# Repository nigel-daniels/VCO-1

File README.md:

# VCO 1

Here is my first VCO based on the work of Moritz Klein and his great series of VCO videos found [here](https://www.youtube.com/watch?v=QBatvo8bCa4&list=PLHeL0JWdJLvTuGCyC3qvx0RM39YvopVQN). I based the schematic on his work and the Erica Synths kit schematic but I added in the sawtooth-to-triangle wave converter. 

The PCB design is my own and I designed it as a two layer pcb made of two double sided pcbs. I ended up self-etching, hence the registration pin-holes next to the drill holes for the standoffs on the pcb designs.

I hope you find this useful, and a huge thanks to Moritz Klein for getting me started down this path!

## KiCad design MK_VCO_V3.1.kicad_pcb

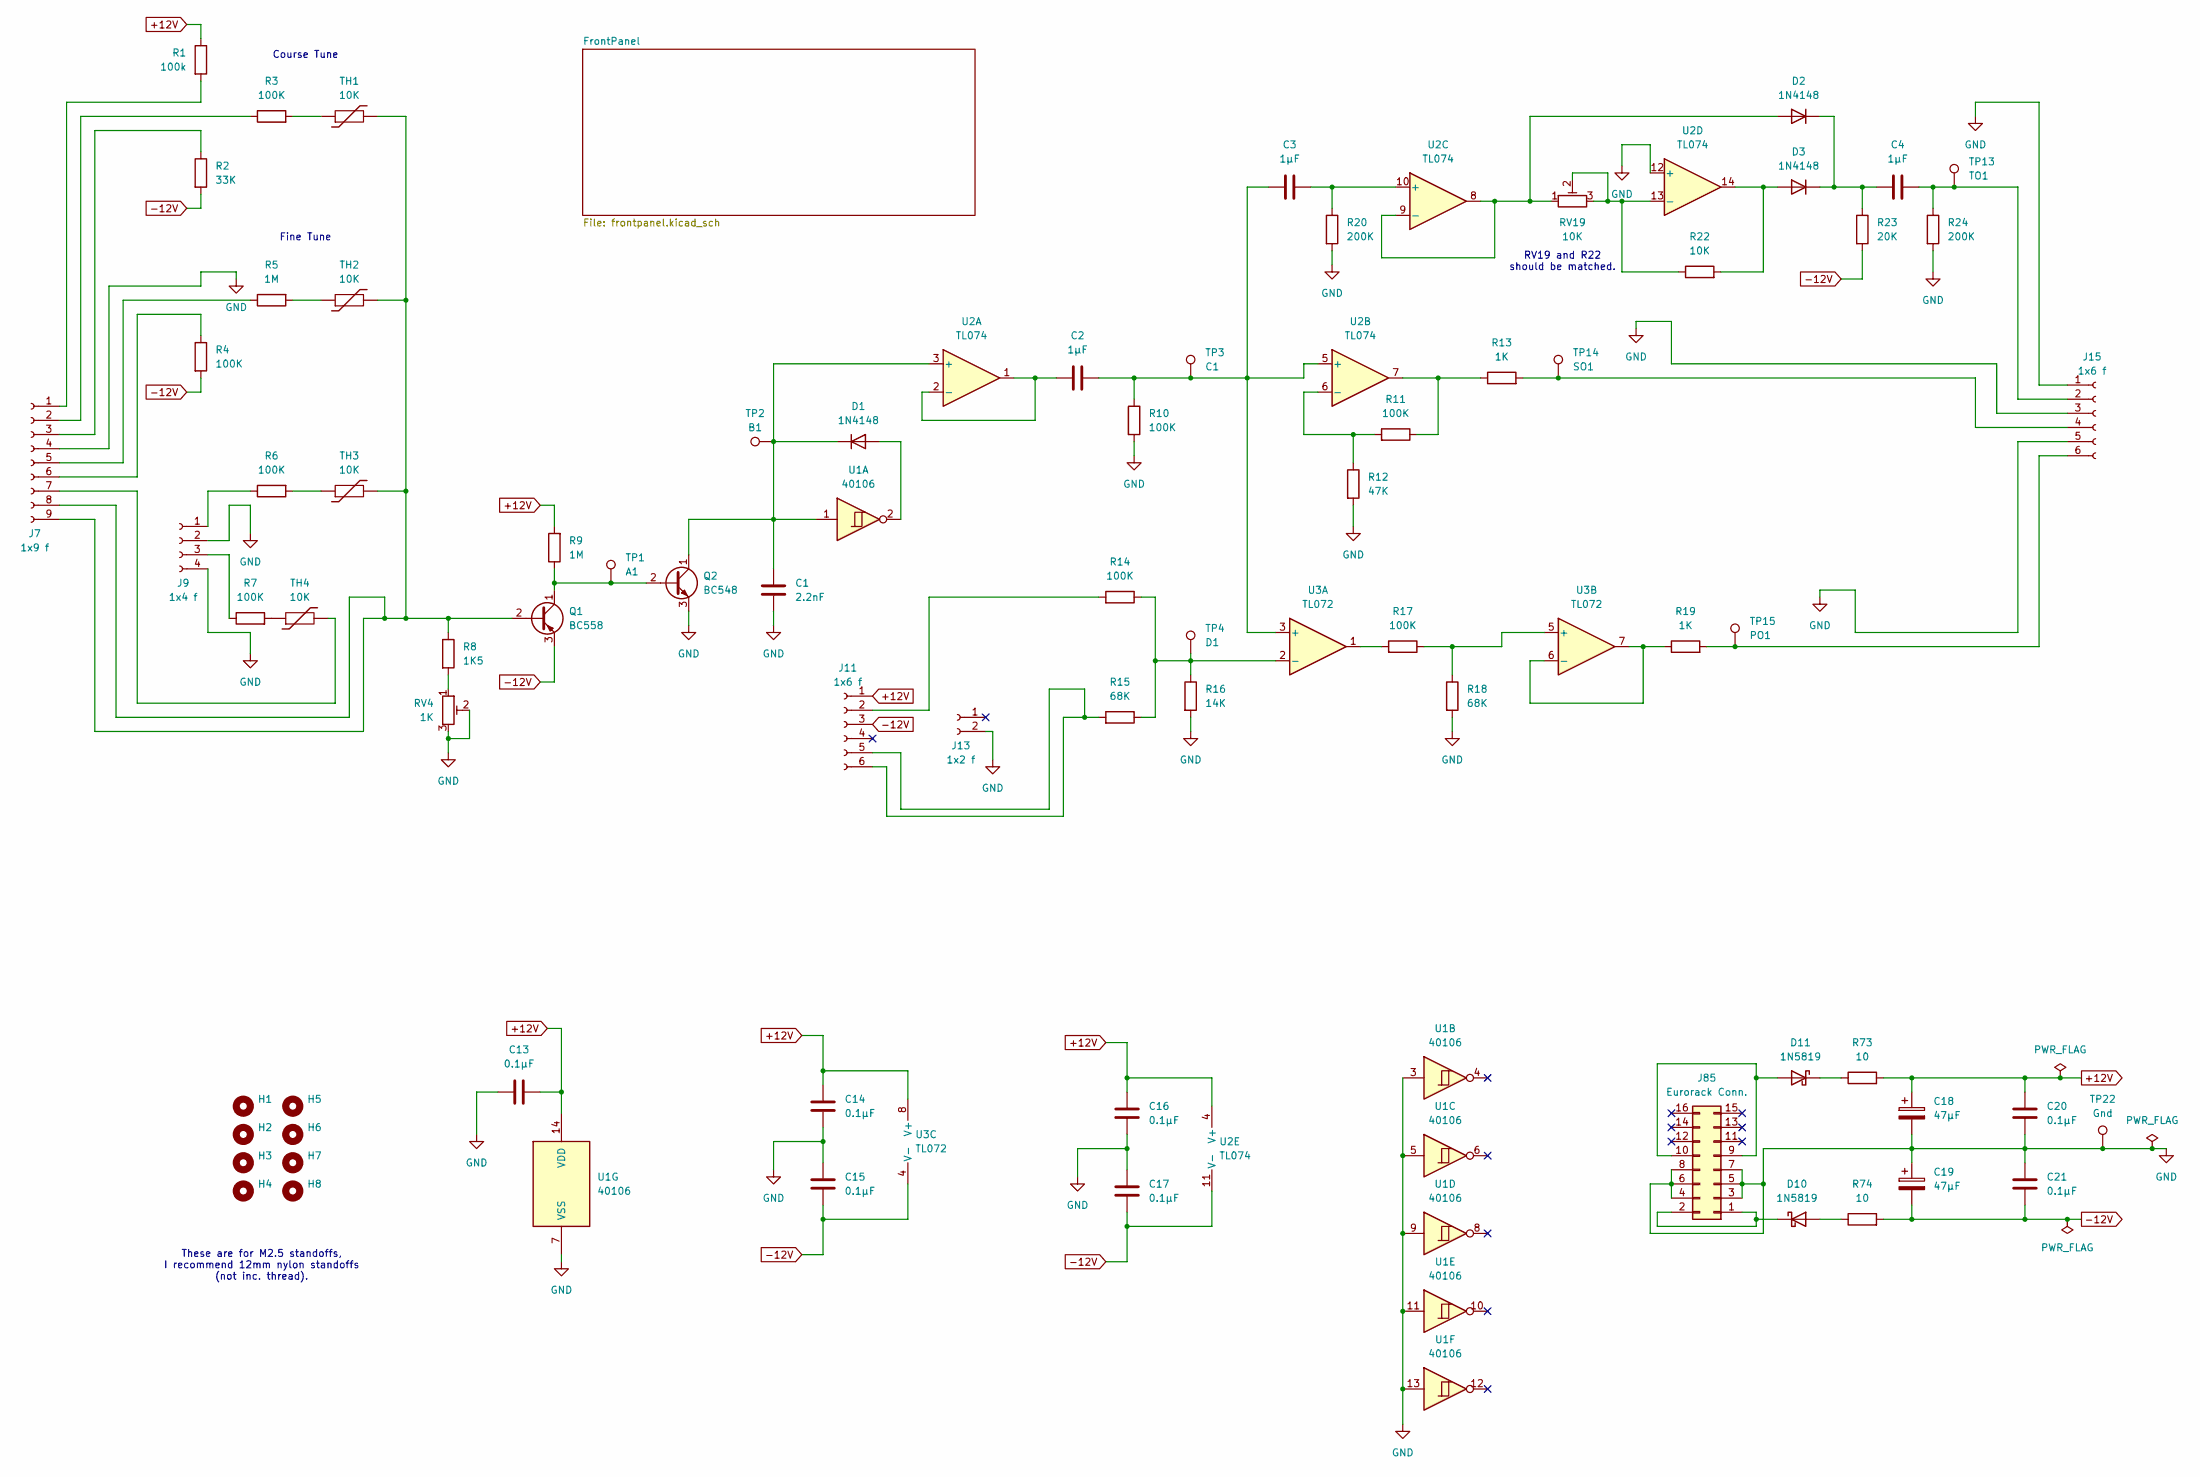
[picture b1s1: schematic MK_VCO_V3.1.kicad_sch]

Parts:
C1: 2.2nF; C_Disc_D4.7mm_W2.5mm_P5.00mm
C2, C3, C4: 1μF; C_Disc_D4.7mm_W2.5mm_P5.00mm
C13, C14, C15, C16, C17, C20, C21: 0.1μF; C_Disc_D4.7mm_W2.5mm_P5.00mm
C18, C19: 47μF; CP_Radial_D5.0mm_P2.50mm
D1: 1N4148; D_DO-35_SOD27_P2.54mm_Vertical_KathodeUp
D2, D3: 1N4148; D_DO-35_SOD27_P7.62mm_Horizontal
D10, D11: 1N5819; D_DO-41_SOD81_P10.16mm_Horizontal
H1, H2, H3, H4, H5, H6, H7, H8: MountingHole_2.7mm_M2.5
J7: 1x9 f; PinSocket_1x09_P2.54mm_Vertical
J9: 1x4 f; PinSocket_1x04_P2.54mm_Vertical
J11, J15: 1x6 f; PinSocket_1x06_P2.54mm_Vertical
J13: 1x2 f; PinSocket_1x02_P2.54mm_Vertical
J85: Eurorack Conn.; PinHeader_2x08_P2.54mm_Vertical
Q1: BC558; TO-92_Inline_Wide
Q2: BC548; TO-92_Inline_Wide
R1: 100k; R_Axial_DIN0204_L3.6mm_D1.6mm_P7.62mm_Horizontal
R2: 33K; R_Axial_DIN0204_L3.6mm_D1.6mm_P7.62mm_Horizontal
R3, R4, R6, R7, R14, R17: 100K; R_Axial_DIN0204_L3.6mm_D1.6mm_P7.62mm_Horizontal
R5, R9: 1M; R_Axial_DIN0204_L3.6mm_D1.6mm_P7.62mm_Horizontal
R8: 1K5; R_Axial_DIN0204_L3.6mm_D1.6mm_P7.62mm_Horizontal
R10, R11: 100K; R_Axial_DIN0204_L3.6mm_D1.6mm_P2.54mm_Vertical
R12: 47K; R_Axial_DIN0204_L3.6mm_D1.6mm_P2.54mm_Vertical
R13: 1K; R_Axial_DIN0204_L3.6mm_D1.6mm_P7.62mm_Horizontal
R15, R18: 68K; R_Axial_DIN0204_L3.6mm_D1.6mm_P2.54mm_Vertical
R16: 14K; R_Axial_DIN0204_L3.6mm_D1.6mm_P7.62mm_Horizontal
R19: 1K; R_Axial_DIN0204_L3.6mm_D1.6mm_P2.54mm_Vertical
R20: 200K; R_Axial_DIN0204_L3.6mm_D1.6mm_P7.62mm_Horizontal
R22: 10K; R_Axial_DIN0204_L3.6mm_D1.6mm_P2.54mm_Vertical
R23: 20K; R_Axial_DIN0204_L3.6mm_D1.6mm_P7.62mm_Horizontal
R24: 200K; R_Axial_DIN0204_L3.6mm_D1.6mm_P2.54mm_Vertical
R73, R74: 10; R_Axial_DIN0204_L3.6mm_D1.6mm_P7.62mm_Horizontal
RV4: 1K; Potentiometer_Bourns_3296W_Vertical
RV19: 10K; Potentiometer_Bourns_3296W_Vertical
TH1, TH2, TH3, TH4: 10K; R_Axial_DIN0204_L3.6mm_D1.6mm_P5.08mm_Horizontal
TP1: A1; TestPoint_Loop_D2.50mm_Drill1.0mm
TP2: B1; TestPoint_Loop_D2.50mm_Drill1.0mm
TP3: C1; TestPoint_Loop_D2.50mm_Drill1.0mm
TP4: D1; TestPoint_Loop_D2.50mm_Drill1.0mm
TP13: TO1; TestPoint_Loop_D2.50mm_Drill1.0mm
TP14: SO1; TestPoint_Loop_D2.50mm_Drill1.0mm
TP15: PO1; TestPoint_Loop_D2.50mm_Drill1.0mm
TP22: Gnd; TestPoint_Loop_D2.50mm_Drill1.0mm
U1: 40106; DIP-14_W7.62mm
U2: TL074; DIP-14_W7.62mm
U3: TL072; DIP-8_W7.62mm

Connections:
+12V: C13.2, C14.1, C16.1, C18.1, C20.1, J11.1, R1.1, R9.2, R73.2, U1.14 (VDD), U2.4 (V+), U3.8 (V+)
-12V: C15.2, C17.2, C19.2, C21.2, J11.3, Q1.3 (E), R2.2, R4.2, R23.2, R74.2, U2.11 (V-), U3.4 (V-)
GND: C1.2, C13.1, C14.2, C15.1, C16.2, C17.1, C18.2, C19.1, C20.2, C21.1, J7.4, J9.2, J9.4, J13.2, J15.1, J15.3, J15.5, J85.3, J85.4, J85.5, J85.6, J85.7, J85.8, Q2.3 (E), R10.2, R12.2, R16.2, R18.2, R20.2, R24.2, RV4.2, RV4.3, TP22.1, U1.3, U1.5, U1.7 (VSS), U1.9, U1.11, U1.13, U2.12 (+)
unnamed: D1.2 (A), U1.2
unnamed: C1.1, D1.1 (K), Q2.1 (C), TP2.1, U1.1, U2.3 (+)
unnamed: D2.2 (A), RV19.1, U2.8, U2.9 (-)
unnamed: C4.2, D2.1 (K), D3.1 (K), R23.1
unnamed: D3.2 (A), R22.2, U2.14
unnamed: D10.2 (A), R74.1
unnamed: D10.1 (K), J85.1, J85.2
unnamed: D11.2 (A), J85.9, J85.10
unnamed: D11.1 (K), R73.1
unnamed: J7.1, R1.2
unnamed: J7.2, R3.1
unnamed: J7.3, R2.1
unnamed: J7.5, R5.1
unnamed: J7.6, R4.1
unnamed: J7.7, TH4.2
unnamed: J7.8, J7.9, Q1.2 (B), R8.1, TH1.2, TH2.2, TH3.2
unnamed: J9.1, R6.1
unnamed: J9.3, R7.1
unnamed: J11.2, R14.2
unnamed: J11.5, J11.6, R15.2
unnamed: C4.1, J15.2, R24.1, TP13.1
unnamed: J15.4, R13.2, TP14.1
unnamed: J15.6, R19.2, TP15.1
unnamed: Q1.1 (C), Q2.2 (B), R9.1, TP1.1
unnamed: R3.2, TH1.1
unnamed: R5.2, TH2.1
unnamed: R6.2, TH3.1
unnamed: R7.2, TH4.1
unnamed: R8.2, RV4.1
unnamed: R11.1, R13.1, U2.7
unnamed: R17.2, U3.1
unnamed: C2.2, U2.1, U2.2 (-)
unnamed: C2.1, C3.2, R10.1, TP3.1, U2.5 (+), U3.3 (+)
unnamed: R11.2, R12.1, U2.6 (-)
unnamed: C3.1, R20.1, U2.10 (+)
unnamed: R22.1, RV19.2, RV19.3, U2.13 (-)
unnamed: R14.1, R15.1, R16.1, TP4.1, U3.2 (-)
unnamed: R17.1, R18.1, U3.5 (+)
unnamed: R19.1, U3.6 (-), U3.7

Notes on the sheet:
Fine Tune
Course Tune
RV19 and R22 should be matched.
These are for M2.5 standoffs, I recommend 12mm nylon standoffs (not inc. thread).

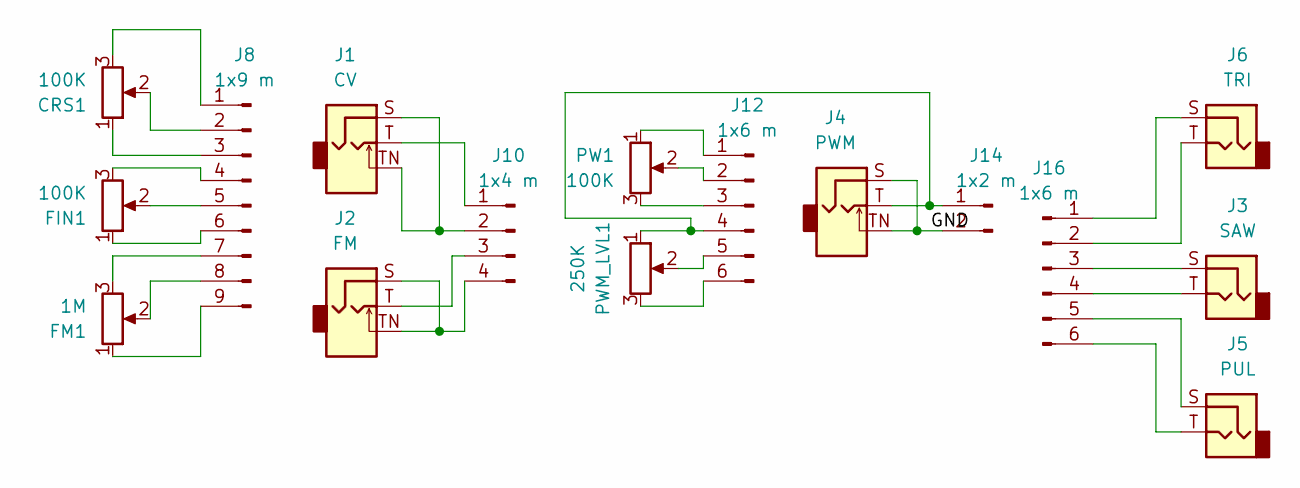
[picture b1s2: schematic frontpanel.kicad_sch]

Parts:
CRS1: 100K; Potentiometer_Alps_RK09L_Single_Vertical
FIN1: 100K; Potentiometer_Alps_RK09L_Single_Vertical
FM1: 1M; Potentiometer_Alps_RK09L_Single_Vertical
J1: CV; Jack_3.5mm_QingPu_WQP-PJ398SM_Vertical_CircularHoles
J2: FM; Jack_3.5mm_QingPu_WQP-PJ398SM_Vertical_CircularHoles
J3: SAW; Jack_3.5mm_QingPu_WQP-PJ398SM_Vertical_CircularHoles
J4: PWM; Jack_3.5mm_QingPu_WQP-PJ398SM_Vertical_CircularHoles
J5: PUL; Jack_3.5mm_QingPu_WQP-PJ398SM_Vertical_CircularHoles
J6: TRI; Jack_3.5mm_QingPu_WQP-PJ398SM_Vertical_CircularHoles
J8: 1x9 m; PinHeader_1x09_P2.54mm_Vertical
J10: 1x4 m; PinHeader_1x04_P2.54mm_Vertical
J12, J16: 1x6 m; PinHeader_1x06_P2.54mm_Vertical
J14: 1x2 m; PinHeader_1x02_P2.54mm_Vertical
PW1: 100K; Potentiometer_Alps_RK09L_Single_Vertical
PWM_LVL1: 250K; Potentiometer_Alps_RK09L_Single_Vertical

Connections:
/FrontPanel/GND: J4.S, J4.TN, J14.2
unnamed: CRS1.3, J8.1
unnamed: CRS1.2, J8.2
unnamed: CRS1.1, J8.3
unnamed: FIN1.3, J8.4
unnamed: FIN1.2, J8.5
unnamed: FIN1.1, J8.6
unnamed: FM1.3, J8.7
unnamed: FM1.2, J8.8
unnamed: FM1.1, J8.9
unnamed: J1.T, J10.1
unnamed: J1.S, J1.TN, J10.2
unnamed: J2.T, J10.3
unnamed: J2.S, J2.TN, J10.4
unnamed: J12.1, PW1.1
unnamed: J12.2, PW1.2
unnamed: J12.3, PW1.3
unnamed: J4.T, J12.4, J14.1, PWM_LVL1.1
unnamed: J12.5, PWM_LVL1.2
unnamed: J12.6, PWM_LVL1.3
unnamed: J6.S, J16.1
unnamed: J6.T, J16.2
unnamed: J3.S, J16.3
unnamed: J3.T, J16.4
unnamed: J5.S, J16.5
unnamed: J5.T, J16.6

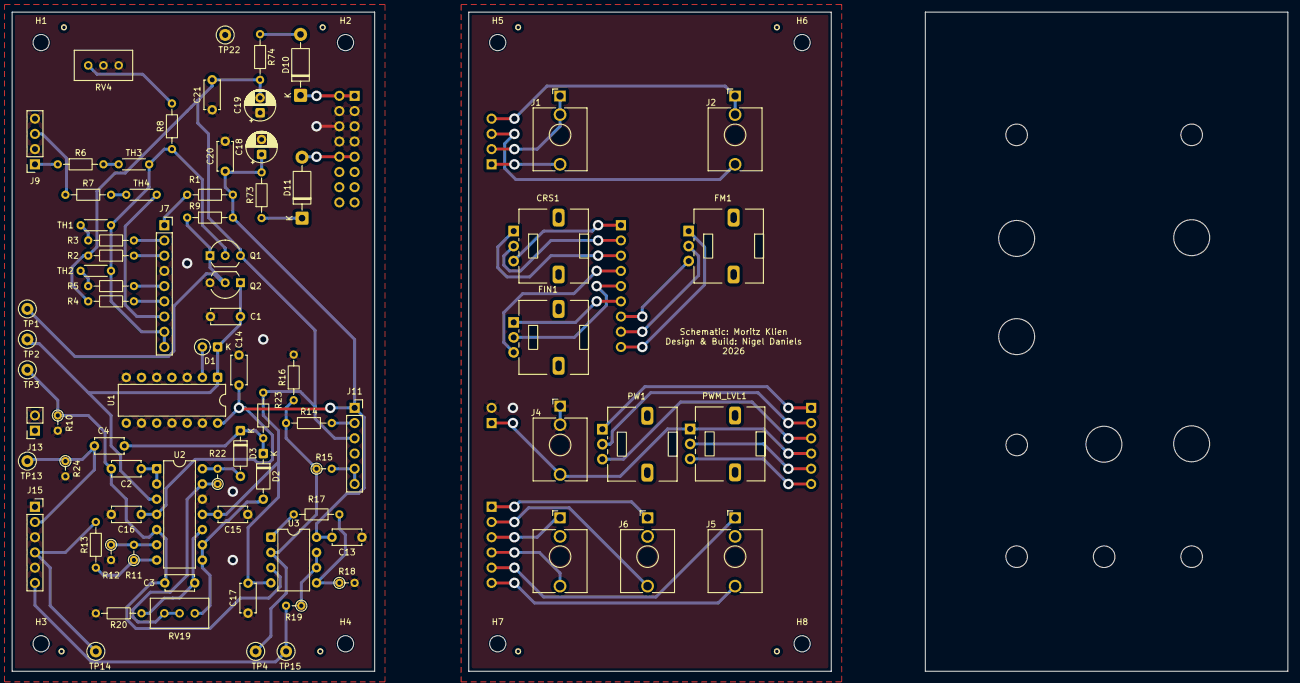
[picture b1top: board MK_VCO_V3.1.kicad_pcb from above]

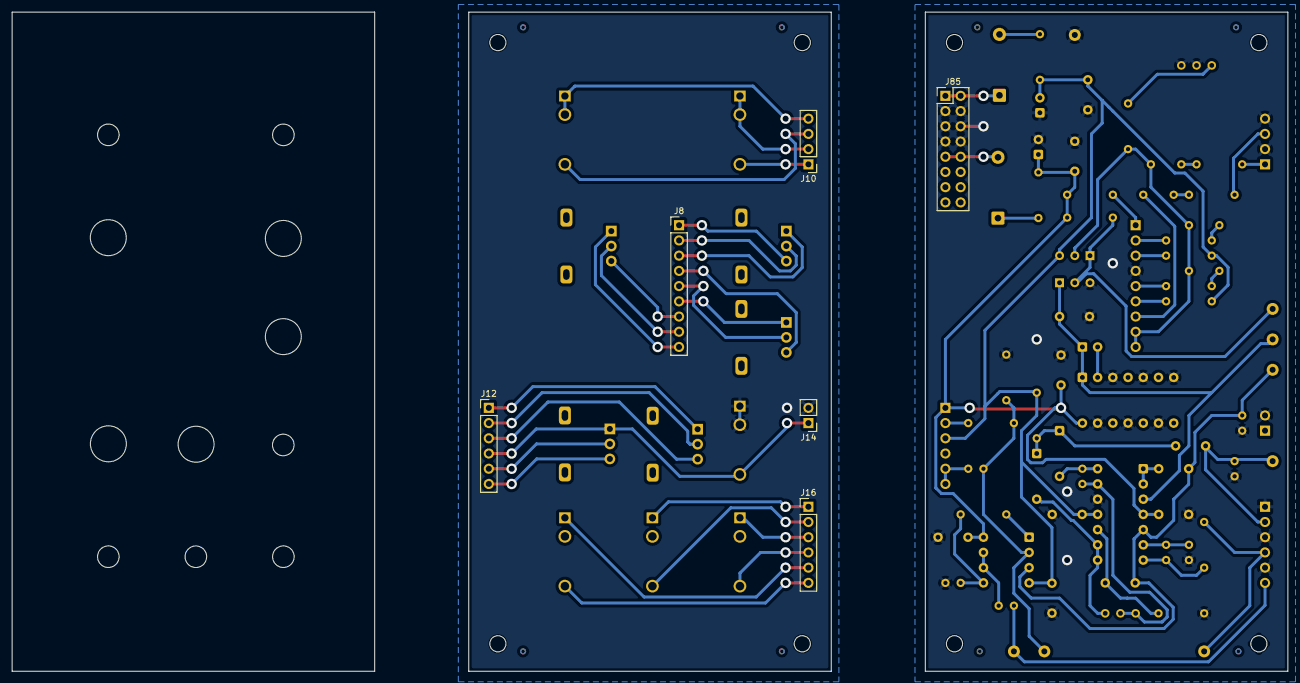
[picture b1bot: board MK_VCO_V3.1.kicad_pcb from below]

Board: 2 copper layers, 60.5 x 110.0 mm, 92 parts (6 on the bottom side), 68 nets.

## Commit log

2026-02-20 Added readme and license.
2026-02-20 Typo
2026-02-22 Fixed inverted pots
2026-02-22 ignore locks
